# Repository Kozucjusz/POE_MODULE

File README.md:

## 1. Introduction
A 100-W Power over Ethernet (PoE) module for device power supply and Ethernet data transmission.
## 2. Key Components:
- 7499511420 WÜRTH - PoE++ Ethernet connector with an integrated transformer, rated for 100 W power.
- PSM040-100MSE - MOSFETs forming active ideal bridge rectifier circuits.
- LT4321 - dual ideal bridge controller for PoE applications.
- LT4320 - single ideal bridge controller, used for the auxiliary power section.
- LT4275 - PoE controller.

## 3. PCB
The designed PCB is divided into two independent functional blocks: PoE and AUX.
The PoE section provides the primary power supply compliant with the Power over Ethernet standard, while the AUX section serves as an alternative, redundant power source intended for operation in the absence of power from the PSE device or in the event of a PoE path failure.

The AUX section allows the module to be powered either from an external DC voltage source or from mains voltage after prior step-down conversion. This solution increases application flexibility and enables the module to be used in systems requiring high power-supply reliability. In cases of space constraints, the AUX section can be mechanically separated—the corresponding part of the PCB may be broken off before component assembly without affecting the correct operation of the PoE section.

The output power of the module can be configured by selecting appropriate resistor values connected to the RCLASS and 4RCLASS++ pins of the LT4275 controller. This allows easy adjustment of the power class to meet specific application requirements without modifying the rest of the design.

To improve energy efficiency and reduce power losses, active bridge rectifiers were used. This approach enables higher output power while significantly reducing thermal losses compared to conventional diode bridges, which is particularly important in ~100 W applications with limited heat dissipation capability.

The use of widened power traces and connection of three connector pins for each power rail ensures safe and stable current flow of up to 1 A without excessive voltage drops or local trace overheating.
Ethernet signal traces were designed with controlled impedance in accordance with differential transmission requirements. Trace widths and spacing between differential pairs were selected to ensure proper characteristic impedance, minimizing signal reflections and preserving signal integrity.

## 4. TEST
Due to the high cost of components required to support the full 100 W power level, the current version of the module has been configured for a maximum output power of 25 W. This allowed verification of the power-supply architecture, the PoE power path, and the overall design assumptions while keeping prototyping costs under control.
For testing purposes, an Ethernet connector compliant with PoE Type 2 was used, enabling safe functional testing and validation of system behavior under conditions corresponding to a lower power class. Configuration of the PoE controller operating parameters is achieved by adjusting the values of the configuration resistors.

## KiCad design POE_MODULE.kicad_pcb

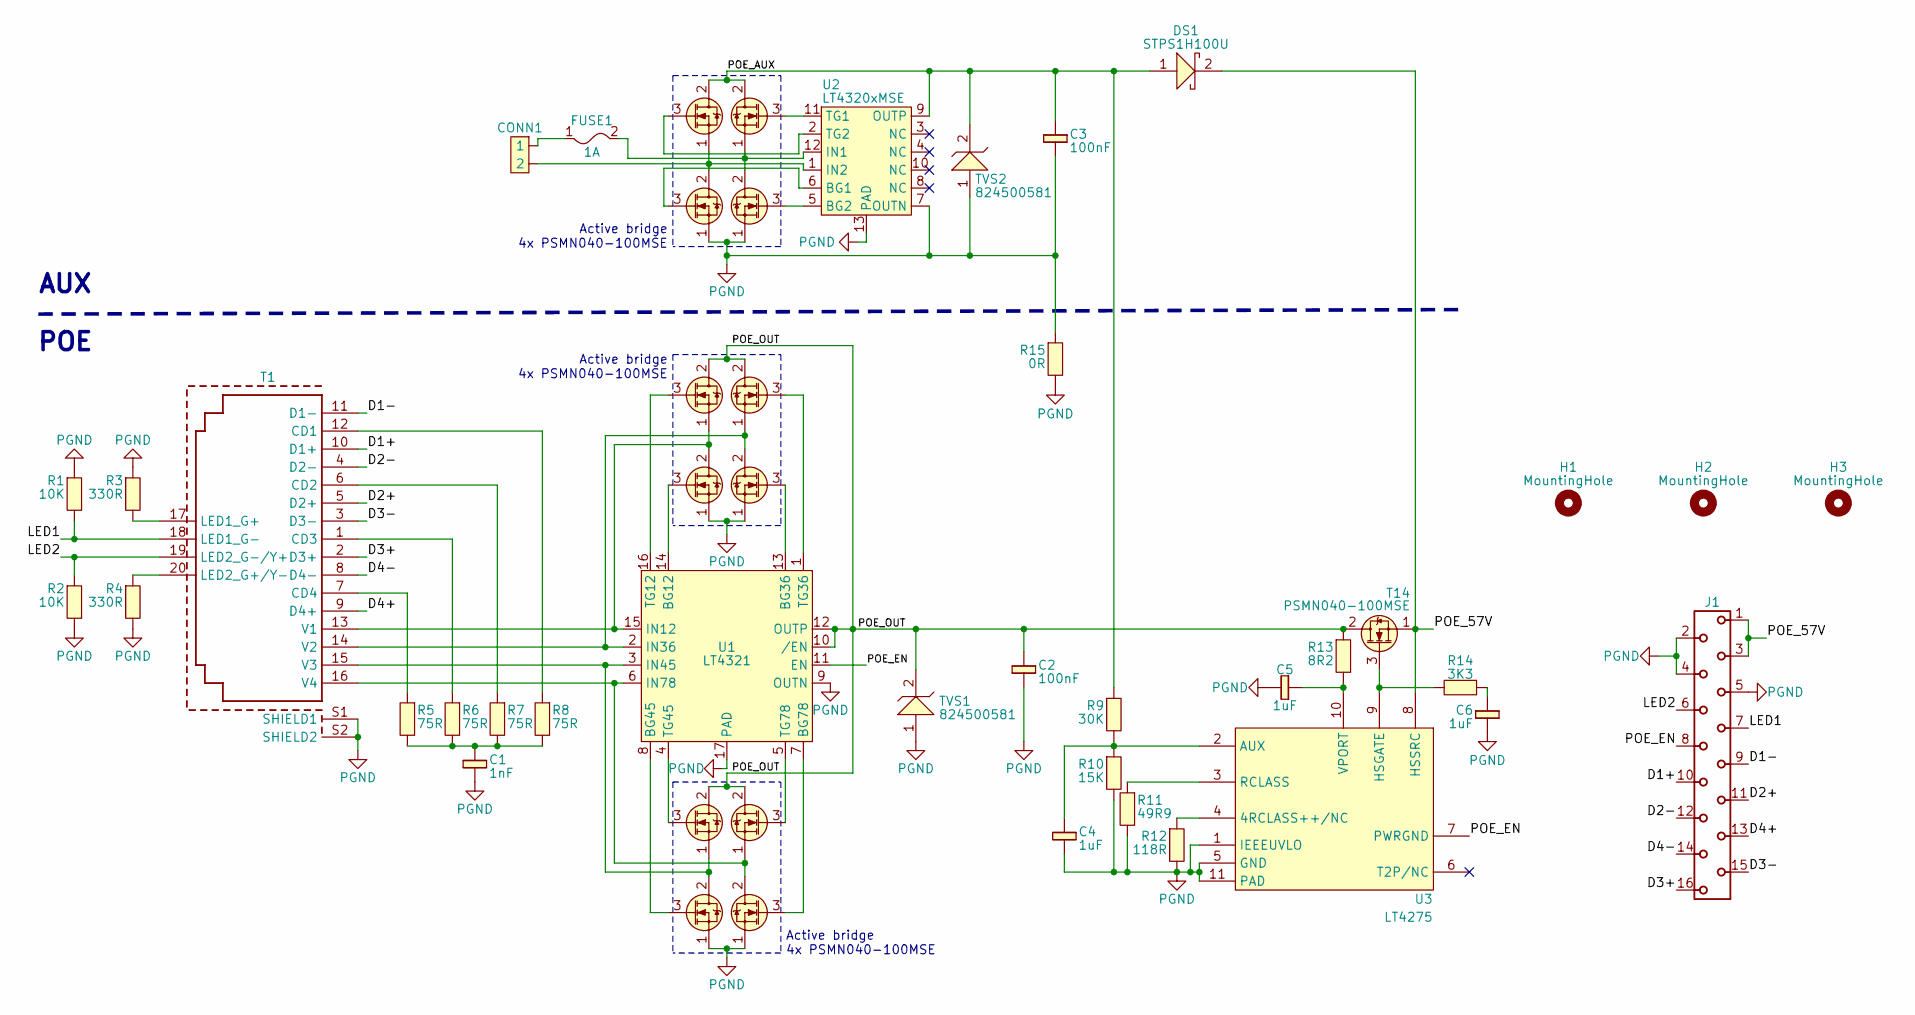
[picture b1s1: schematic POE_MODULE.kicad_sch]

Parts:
C1: 1nF; RLC_0603_1608Metric
C2, C3: 100nF; RLC_1206_3216Metric
C4, C5, C6: 1uF; RLC_1206_3216Metric
CONN1: PhoenixContact_MC_1,5_2-G-3.81_1x02_P3.81mm_Horizontal
DS1: STPS1H100U; D_SMB_Handsoldering
FUSE1: 1A; RLC_2512_6432Metric
H1, H2, H3: MountingHole; MOUNT_HOLE
J1: 690368171672; J_Wurth_WR-MM_690368171672; Working Voltage (V (AC)) 250
R1, R2: 10K; RLC_0603_1608Metric
R3, R4: 330R; RLC_0603_1608Metric
R5, R6, R7, R8: 75R; RLC_0603_1608Metric
R9: 30K; RLC_1206_3216Metric
R10: 15K; RLC_1206_3216Metric
R11: 49R9; RLC_1206_3216Metric
R12: 118R; RLC_1206_3216Metric
R13: 8R2; RLC_1206_3216Metric
R14: 3K3; RLC_1206_3216Metric
R15: 0R; RLC_1206_3216Metric
T1: 7499511420; T_Wurth_WE-RJ45LAN_7499511420; Part Number 7499511420
T2, T3, T4, T5, T6, T7, T8, T9, T10, T11, T12, T13, T14: PSMN040-100MSE; LFPAK33
TVS1, TVS2: 824500581; D_SMA_Handsoldering
U1: LT4321; QFN-16-1EP_4x4mm_P0.65mm_EP2.1x2.1mm_ThermalVias
U2: LT4320xMSE; MSOP-12-1EP_3x4.039mm_P0.65mm_EP1.651x2.845mm_ThermalVias
U3: LT4275; MSOP-10-1EP_3x3mm_P0.5mm_EP2.2x3.1mm_Mask1.83x1.89mm_Therma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

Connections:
/D1+: J1.10, T1.10 (D1+)
/D1-: J1.9, T1.11 (D1-)
/D2+: J1.11, T1.5 (D2+)
/D2-: J1.12, T1.4 (D2-)
/D3+: J1.16, T1.2 (D3+)
/D3-: J1.15, T1.3 (D3-)
/D4+: J1.13, T1.9 (D4+)
/D4-: J1.14, T1.8 (D4-)
/LED1: J1.7, R1.2, T1.18 (LED1_G-)
/LED2: J1.6, R2.1, T1.19 (LED2_G-/Y+)
/POE_57V: DS1.2, J1.1, J1.3, T14.1 (Source), U3.8 (HSSRC)
/POE_AUX: C3.1, DS1.1, R9.1, T2.2 (Drain), T8.2 (Drain), TVS2.2, U2.9 (OUTP)
/POE_EN: J1.8, U1.11 (EN), U3.7 (PWRGND)
/POE_OUT: C2.1, R13.1, T4.2 (Drain), T6.2 (Drain), T10.2 (Drain), T12.2 (Drain), T14.2 (Drain), TVS1.2, U1.10 (/EN), U1.12 (OUTP)
unnamed: C1.1, R5.2, R6.2, R7.2, R8.2
unnamed: C6.1, R14.1
unnamed: CONN1.1, FUSE1.1
unnamed: R8.1, T1.12 (CD1)
unnamed: R7.1, T1.6 (CD2)
unnamed: R6.1, T1.1 (CD3)
unnamed: R5.1, T1.7 (CD4)
unnamed: R3.2, T1.17 (LED1_G+)
unnamed: R4.1, T1.20 (LED2_G+/Y-)
unnamed: T1.13 (V1), T4.1 (Source), T5.2 (Drain), U1.15 (IN12)
unnamed: T1.14 (V2), T10.1 (Source), T11.2 (Drain), U1.2 (IN36)
unnamed: T1.15 (V3), T6.1 (Source), T7.2 (Drain), U1.3 (IN45)
unnamed: T1.16 (V4), T12.1 (Source), T13.2 (Drain), U1.6 (IN78)
unnamed: T2.3 (Gate), U2.2 (TG2)
unnamed: CONN1.2, T2.1 (Source), T3.2 (Drain), U2.1 (IN2)
unnamed: T3.3 (Gate), U2.6 (BG1)
unnamed: T4.3 (Gate), U1.16 (TG12)
unnamed: T5.3 (Gate), U1.14 (BG12)
unnamed: T6.3 (Gate), U1.4 (TG45)
unnamed: T7.3 (Gate), U1.8 (BG45)
unnamed: T8.3 (Gate), U2.11 (TG1)
unnamed: FUSE1.2, T8.1 (Source), T9.2 (Drain), U2.12 (IN1)
unnamed: T9.3 (Gate), U2.5 (BG2)
unnamed: T10.3 (Gate), U1.1 (TG36)
unnamed: T11.3 (Gate), U1.13 (BG36)
unnamed: T12.3 (Gate), U1.5 (TG78)
unnamed: T13.3 (Gate), U1.7 (BG78)
unnamed: R14.2, T14.3 (Gate), U3.9 (HSGATE)
unnamed: R12.1, U3.4 (4RCLASS++/NC)
unnamed: C4.1, R9.2, R10.1, U3.2 (AUX)
unnamed: R11.1, U3.3 (RCLASS)
unnamed: C5.1, R13.2, U3.10 (VPORT)
PGND: C1.2, C2.2, C3.2, C4.2, C5.2, C6.2, J1.2, J1.4, J1.5, R1.1, R2.2, R3.1, R4.2, R10.2, R11.2, R12.2, R15.1, R15.2, T1.S1 (SHIELD1), T1.S2 (SHIELD2), T3.1 (Source), T5.1 (Source), T7.1 (Source), T9.1 (Source), T11.1 (Source), T13.1 (Source), TVS1.1, TVS2.1, U1.9 (OUTN), U1.17 (PAD), U2.7 (OUTN), U2.13 (PAD), U3.1 (IEEEUVLO), U3.5 (GND), U3.11 (PAD)

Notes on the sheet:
AUX POE
Active bridge 4x PSMN040-100MSE

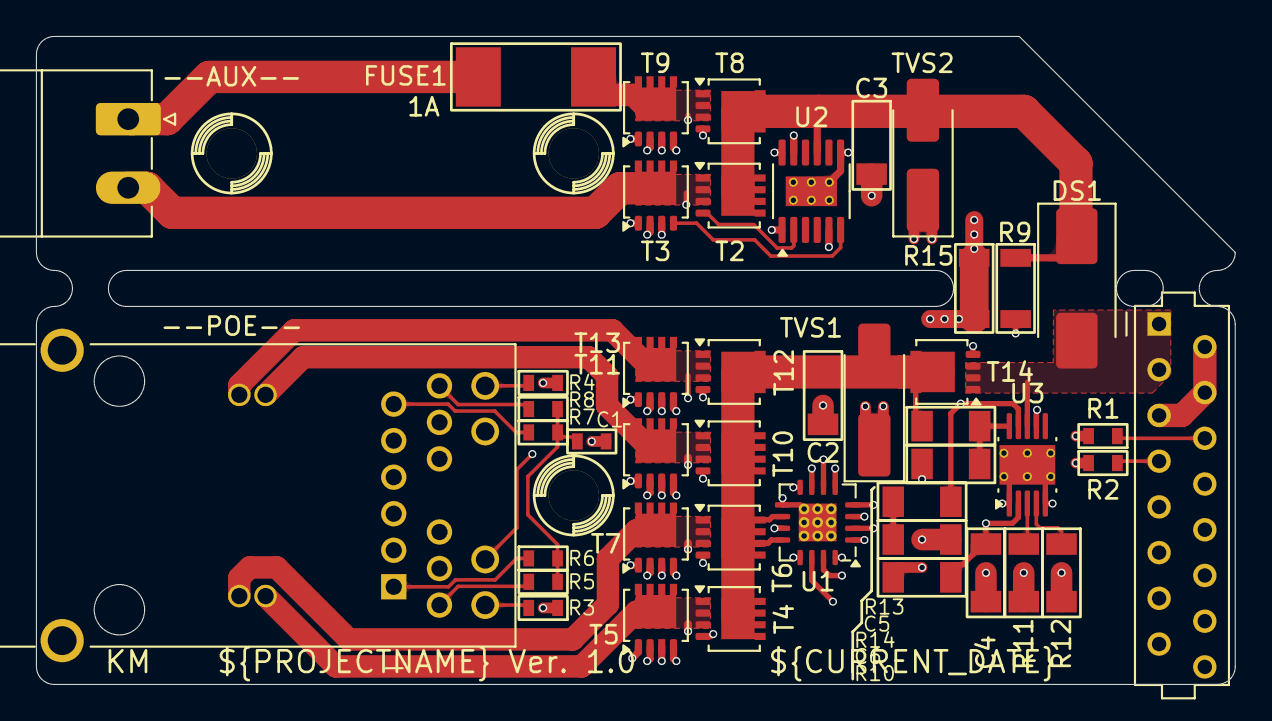
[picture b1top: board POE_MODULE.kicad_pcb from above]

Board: 4 copper layers, 66.6 x 36.0 mm, 47 parts (0 on the bottom side), 47 nets.

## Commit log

2026-02-26 readme update
2026-02-26 img rotate
